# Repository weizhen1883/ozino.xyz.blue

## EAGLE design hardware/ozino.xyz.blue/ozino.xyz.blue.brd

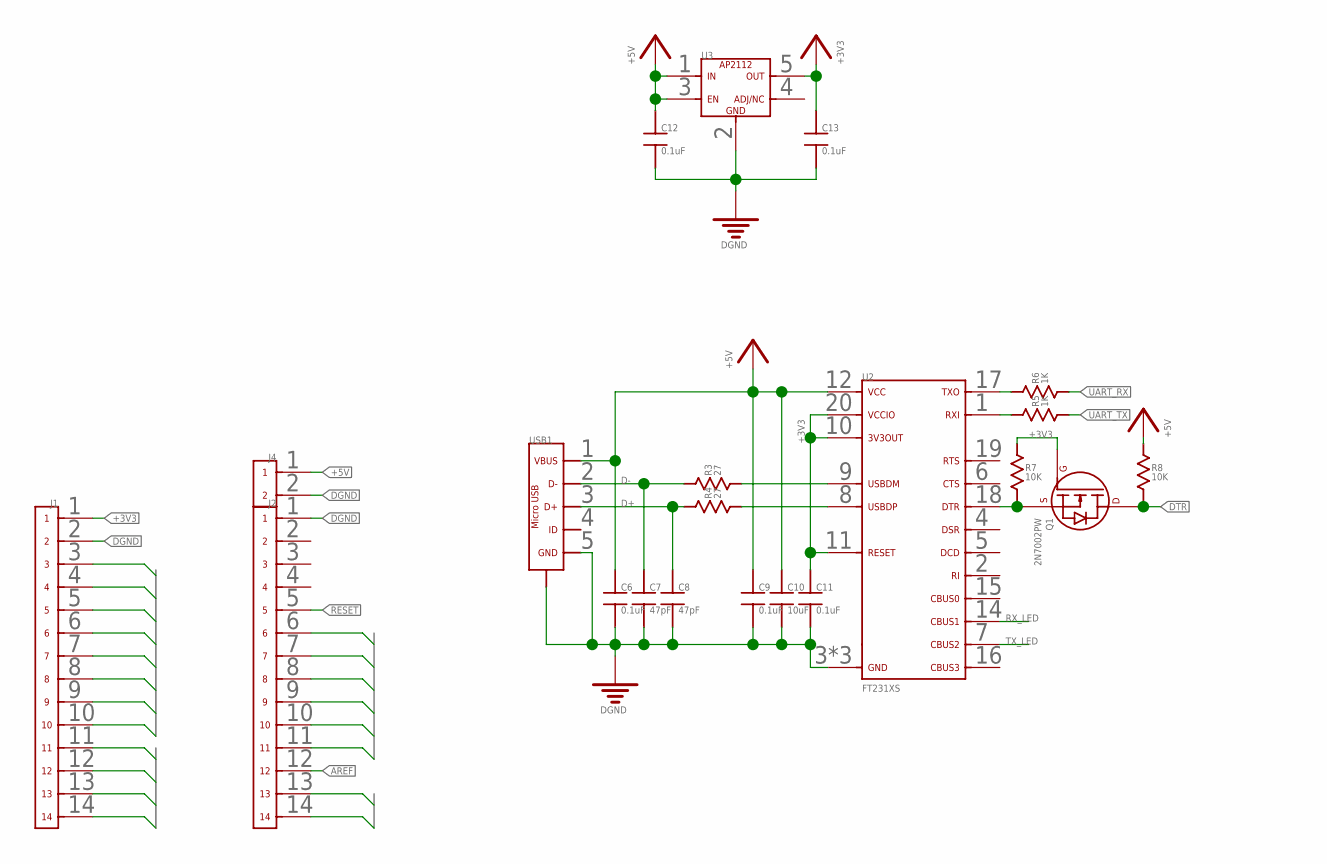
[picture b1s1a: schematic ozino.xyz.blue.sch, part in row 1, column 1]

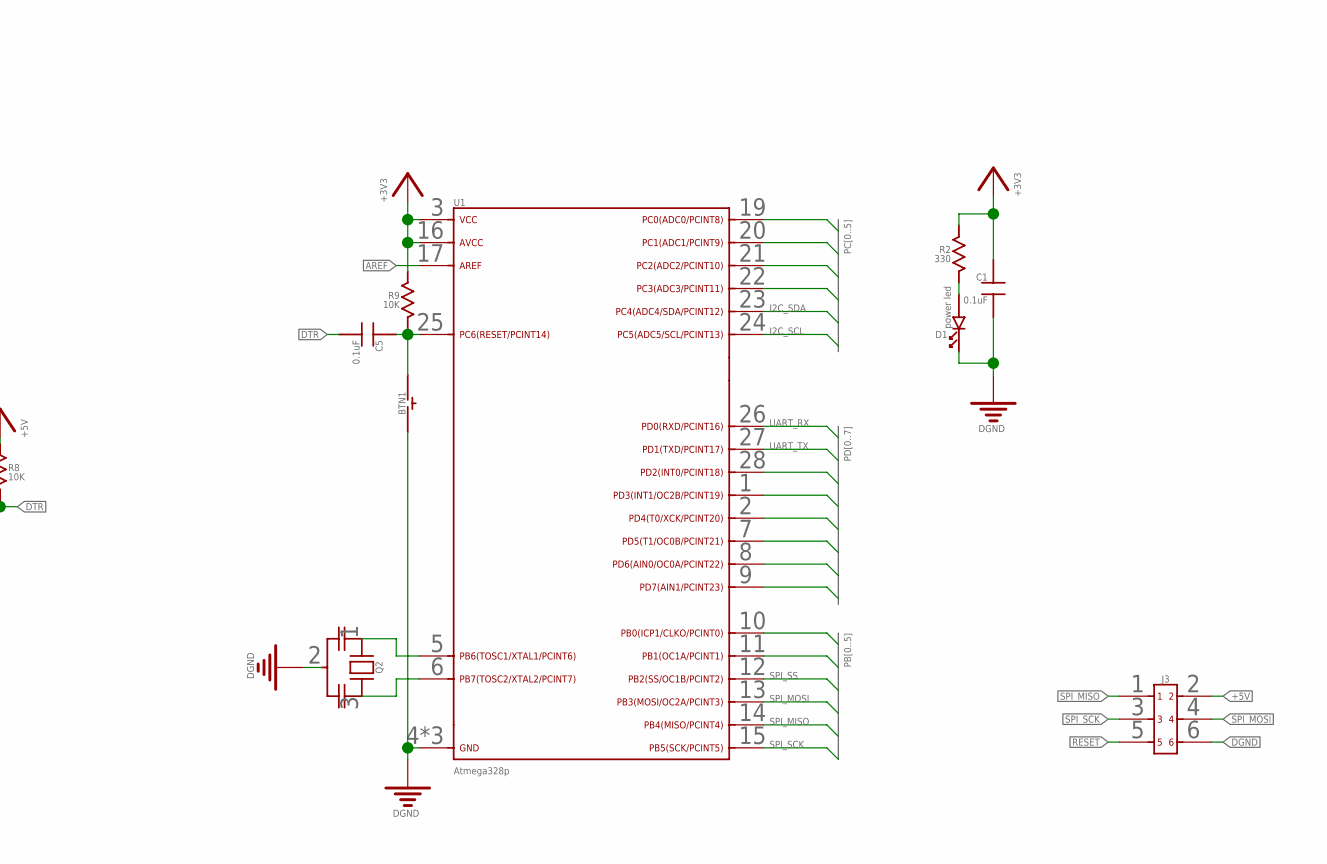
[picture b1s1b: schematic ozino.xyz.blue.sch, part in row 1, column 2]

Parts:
BTN1: BTN_NORMAL_OFF_6_3.5_SMD; BTN_6_3.5_SMD
C1, C5, C6, C9, C11, C12, C13: 0.1uF; 0402
C7, C8: 47pF; 0402
C10: 10uF; 0402
D1: power led; 0805DIODE
J1, J2: 14PIN_HEADER_PITCH2.54MM_TH
J3: 6PIN_2ROW_TC2030_NL; TC2030_NL
J4: 2PIN_HEADER_PITCH2.54MM_TH
Q1: 2N7002PW; SOT323(SC-70)
Q2: RESONATORS; CXTCE_____V
R2: 330; 0805
R3, R4: 27; 0402
R5, R6: 1K; 0402
R7, R8, R9: 10K; 0402
U1: Atmega328p; QFN-28
U2: FT231XS_WFQFN20; WFQFN-20
U3: AP2112K_SOT-23-5; SOT-23-5
USB1: USB-2.0-MICRO_SMD_SMD; MICRO-USB-B-SMD-SMD

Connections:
+3V3: C1.1, C11.1, C13.1, J1.1, Q1.1 (G), R2.1, R7.1, R9.1, U1.3 (VCC), U1.16 (AVCC), U2.10 (3V3OUT), U2.11 (RESET), U2.20 (VCCIO), U3.5
+5V: C6.1, C9.1, C10.1, C12.1, J3.2, J4.1, R8.1, U2.12 (VCC), U3.1, U3.3, USB1.1 (VBUS)
AREF: J2.12, U1.17 (AREF)
D+: C8.1, R4.1, USB1.3 (D+)
D-: C7.1, R3.1, USB1.2 (D-)
DGND: BTN1.1, C1.2, C6.2, C7.2, C8.2, C9.2, C10.2, C11.2, C12.2, C13.2, D1.1 (K), J1.2, J2.1, J3.6, J4.2, Q2.2, U1.4 (GND), U1.18 (GND), U1.T (GND), U2.3 (GND), U2.13 (GND), U2.T (GND), U3.2, USB1.5 (GND), USB1.M1 (SHIELD), USB1.M2 (SHIELD), USB1.M3 (SHIELD), USB1.M4 (SHIELD), USB1.S1 (SHIELD), USB1.S2 (SHIELD)
DTR: C5.2, Q1.3 (D), R8.2
I2C_SCL: J2.6, U1.24 (PC5)
I2C_SDA: J2.7, U1.23 (PC4)
unnamed: R3.2, U2.9 (USBDM)
unnamed: R4.2, U2.8 (USBDP)
unnamed: R6.1, U2.17 (TXD)
unnamed: R5.1, U2.1 (RXD)
unnamed: Q2.1, U1.5 (PB6)
unnamed: Q2.3, U1.6 (PB7)
unnamed: Q1.2 (S), R7.2, U2.18 (DTR)
unnamed: D1.2 (A), R2.2
PB0: J1.11, U1.10 (PB0)
PB1: J1.12, U1.11 (PB1)
PC0: J2.11, U1.19 (PC0)
PC1: J2.10, U1.20 (PC1)
PC2: J2.9, U1.21 (PC2)
PC3: J2.8, U1.22 (PC3)
PD2: J1.5, U1.28 (PD2)
PD3: J1.6, U1.1 (PD3)
PD4: J1.7, U1.2 (PD4)
PD5: J1.8, U1.7 (PD5)
PD6: J1.9, U1.8 (PD6)
PD7: J1.10, U1.9 (PD7)
RESET: BTN1.2, C5.1, J2.5, J3.5, R9.2, U1.25 (PC6)
RX_LED: U2.14 (CBUS1)
SPI_MISO: J2.14, J3.1, U1.14 (PB4)
SPI_MOSI: J1.14, J3.4, U1.13 (PB3)
SPI_SCK: J2.13, J3.3, U1.15 (PB5)
SPI_SS: J1.13, U1.12 (PB2)
TX_LED: U2.7 (CBUS2)
UART_RX: J1.3, R6.2, U1.26 (PD0)
UART_TX: J1.4, R5.2, U1.27 (PD1)

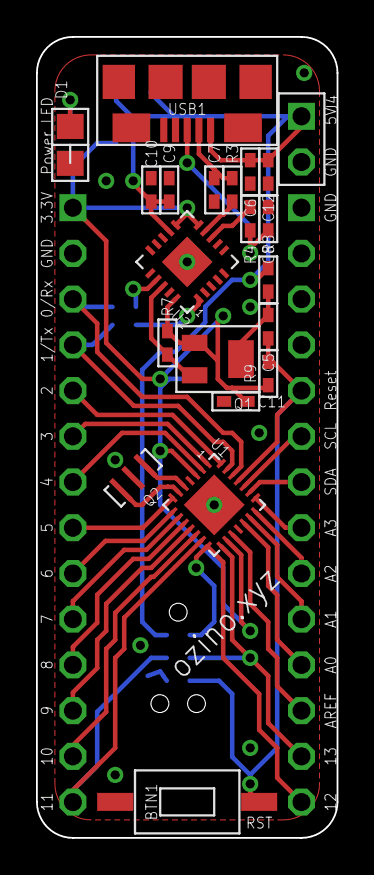
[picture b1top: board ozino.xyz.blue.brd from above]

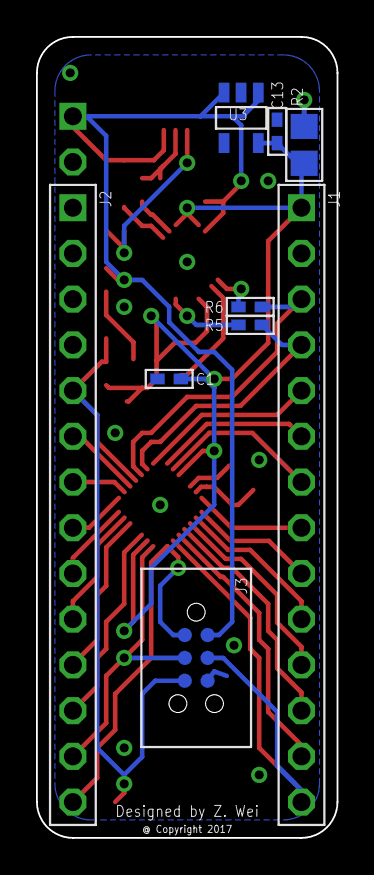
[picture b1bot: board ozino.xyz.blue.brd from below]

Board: 2 copper layers, 16.7 x 44.5 mm, 30 parts (9 on the bottom side), 36 nets.

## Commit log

2017-09-10 v1 updated

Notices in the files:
hardware/ozino.xyz.blue/ozino.xyz.blue.brd:
@ Copyright 2017
